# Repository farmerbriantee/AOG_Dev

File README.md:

# AOG Development

Like AgOpenGPS but not.<br>
This version is constantly under development.<br>
Some differences:<br>
The fields and vehicles are **not** backwards compatible. They are stored in ```C:\Documents\AOG```, not ```C:\Documents\AgOpenGPS``` like previous versions were. 

Instead of one vehicle file where everything was stored, there is now a "User" file where the display settings are stored, regardless of which vehicle is used. The Vehicle and Tool are also separated, so you can have one vehicle per tractor, and a Tool for each implement. Fields are also changed, so you can have multiple Jobs per field, saving you from needing to create "Fields From Existing". The painted area is saved in the Job file, and can be re-opened whenever you want. 

AOG also supports the TM 171 IMU via USB. 

AOG also has builtin Rate Control.

AOG also has builtin Active Tool Steering.

AgIO natively supports GPS Out via serial bus, so the GPS_Out application is not required.

There are other minor differences, but these are the main ones.

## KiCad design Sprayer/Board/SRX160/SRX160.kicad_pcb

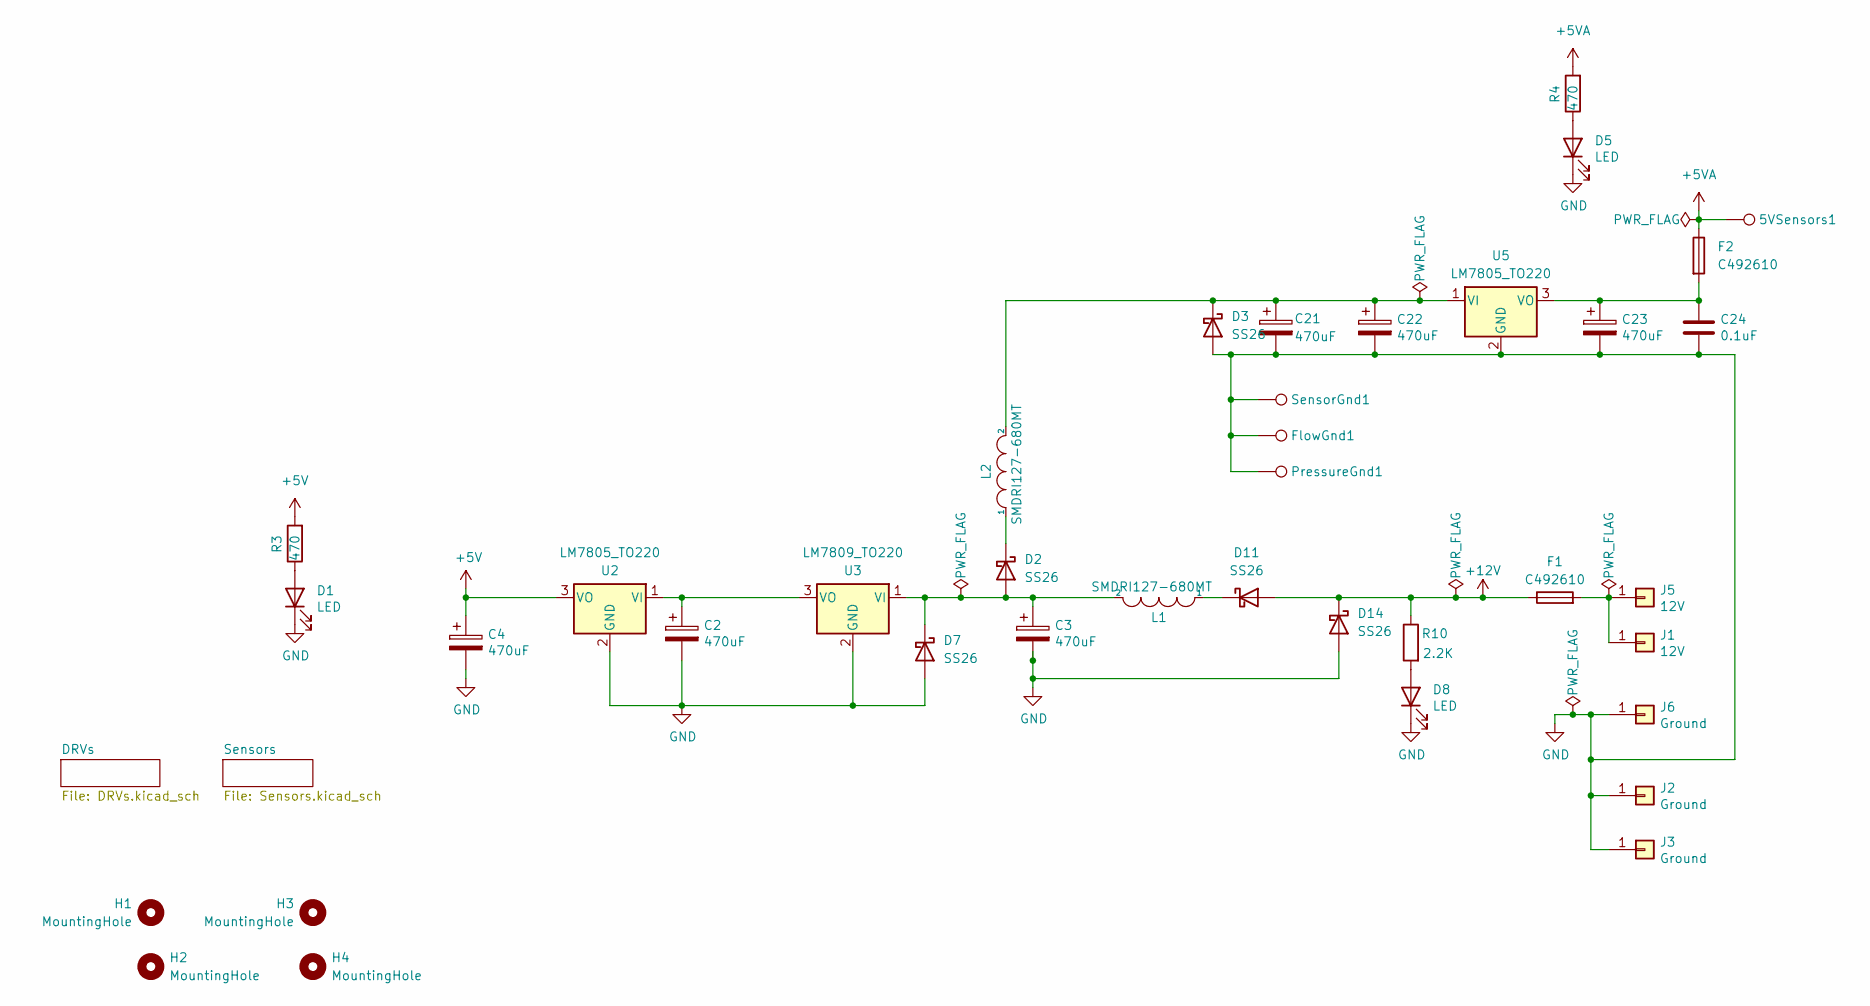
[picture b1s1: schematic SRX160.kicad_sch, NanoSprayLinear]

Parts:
5VSensors1: WirePad; SolderWirePad16
C2, C3, C4, C21, C22, C23: 470uF; CP_Elec_10x10.5
C24: 0.1uF; C_0603_1608Metric
D1, D5, D8: LED; LED_0603_1608Metric
D2, D3, D7, D11, D14: SS26; D_SMA
F1, F2: C492610; Fuse_Holder_C492610
FlowGnd1: WirePad; SolderWirePad16
H1, H2, H3, H4: MountingHole; MountingHole_5.3mm_M5_DIN965_Pad
J1, J5: 12V; PowerPin
J2, J3, J6: Ground; PowerPin
L1, L2: SMDRI127-680MT; TMPA1265SP-101MN-D
PressureGnd1: WirePad; SolderWirePad16
R3, R4: 470; R_0603_1608Metric
R10: 2.2K; R_0603_1608Metric
SensorGnd1: WirePad; SolderWirePad16
U2, U5: LM7805_TO220; TO-220-3_Vertical
U3: LM7809_TO220; TO-220-3_Vertical

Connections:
+5V: C4.1, R3.2, U2.3 (VO); also elsewhere on the board
+5VA: 5VSensors1.1, F2.1, R4.2; also elsewhere on the board
+12V: D11.2 (A), D14.1 (K), F1.1, R10.1; also elsewhere on the board
GND: C2.2, C3.2, C4.2, C21.2, C22.2, C23.2, C24.2, D1.1 (K), D3.2 (A), D5.1 (K), D7.2 (A), D8.1 (K), D14.2 (A), FlowGnd1.1, J2.1, J3.1, J6.1, PressureGnd1.1, SensorGnd1.1, U2.2 (GND), U3.2 (GND), U5.2 (GND); also elsewhere on the board
unnamed: D1.2 (A), R3.1
unnamed: C3.1, D2.2 (A), D7.1 (K), L1.2, U3.1 (VI)
unnamed: D2.1 (K), L2.1
unnamed: C21.1, C22.1, D3.1 (K), L2.2, U5.1 (VI)
unnamed: D5.2 (A), R4.1
unnamed: D8.2 (A), R10.2
unnamed: D11.1 (K), L1.1
unnamed: F1.2, J1.1, J5.1
unnamed: C2.1, U2.1 (VI), U3.3 (VO)
unnamed: C23.1, C24.1, F2.2, U5.3 (VO)

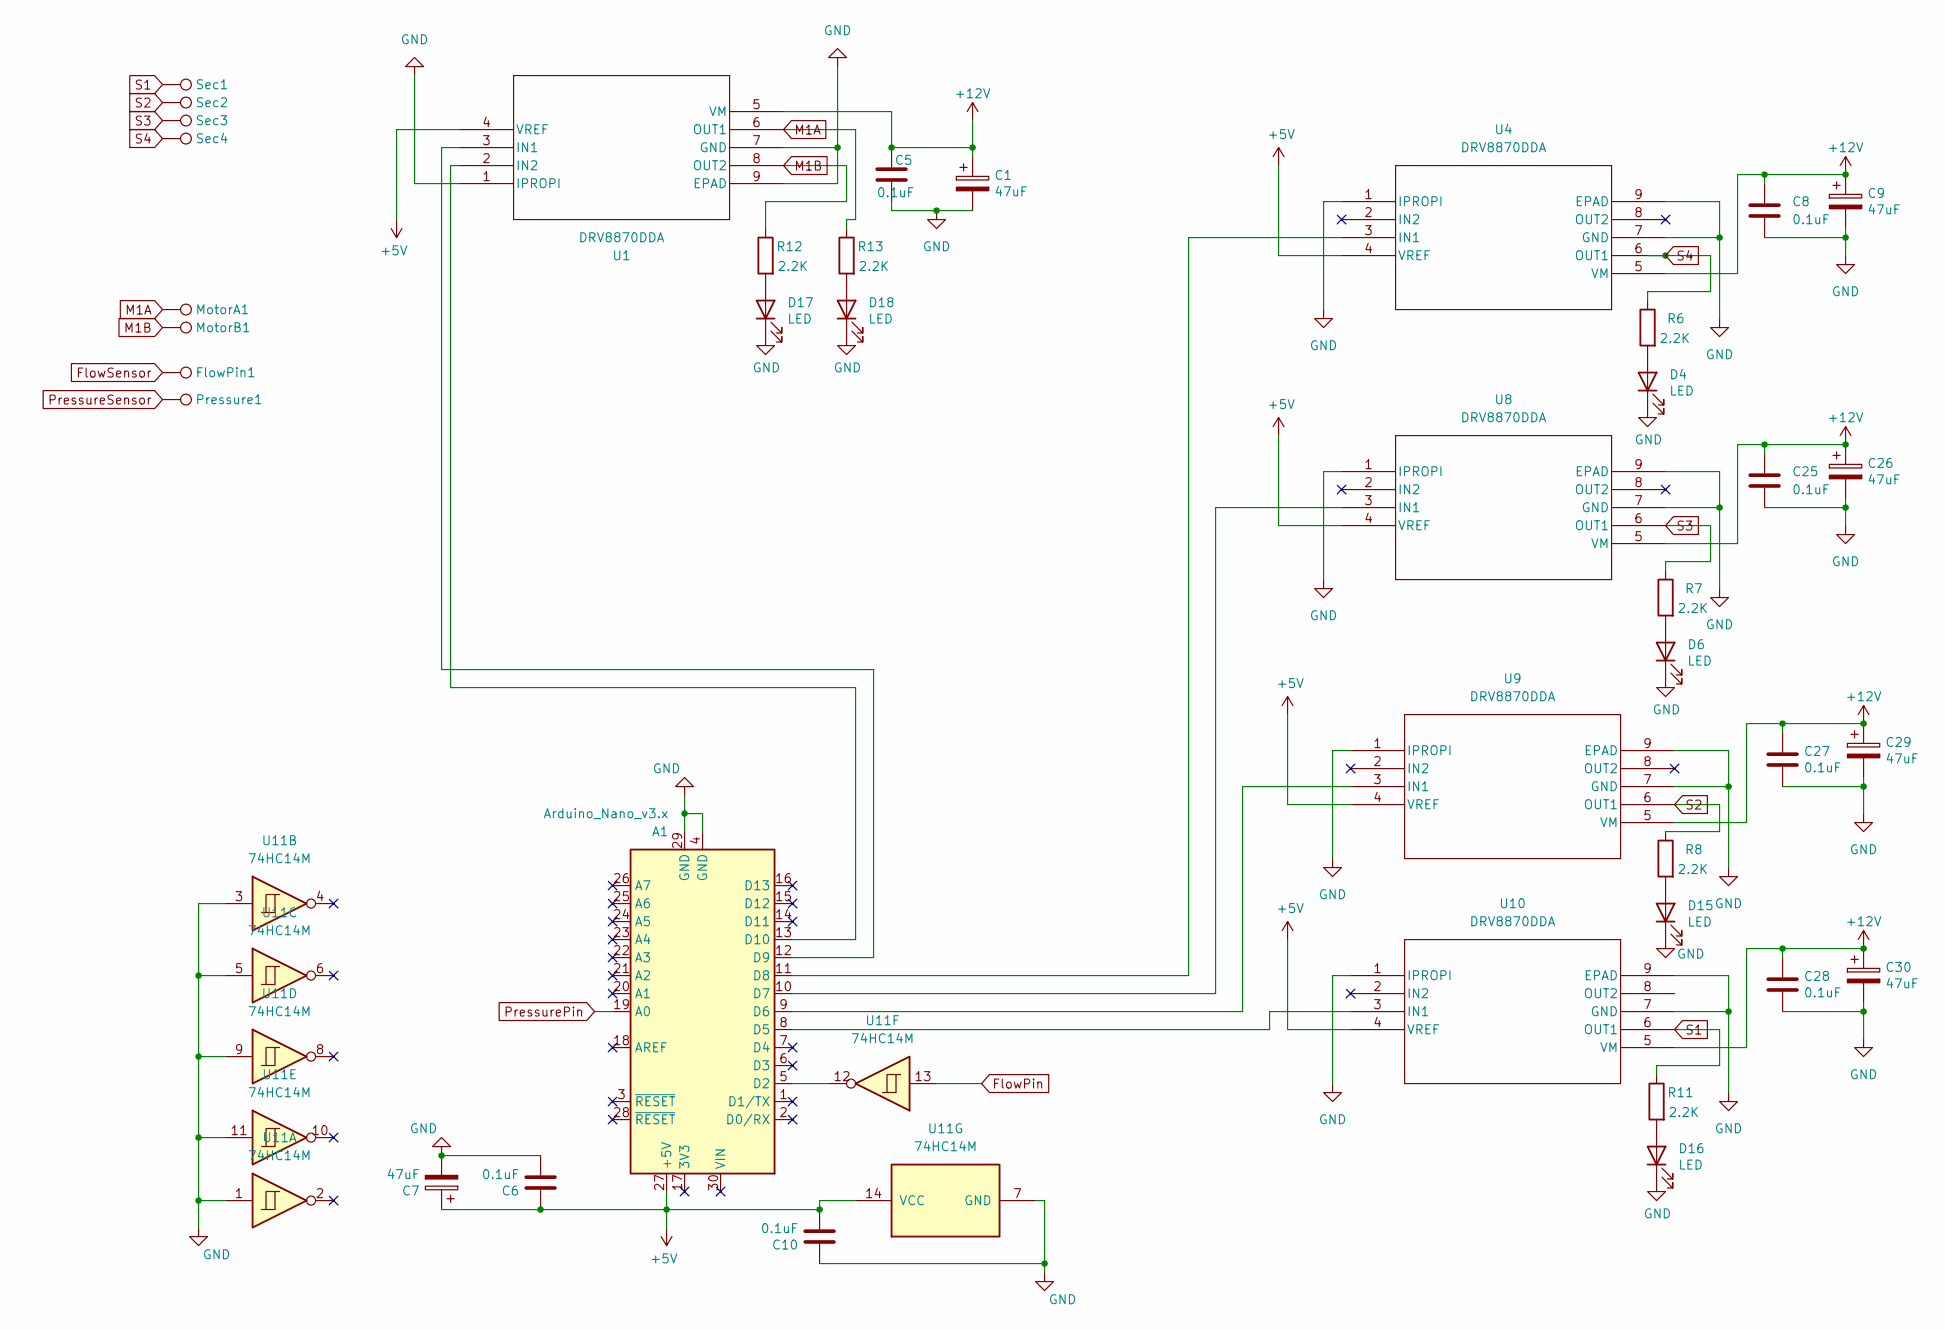
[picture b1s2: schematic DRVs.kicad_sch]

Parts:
A1: Arduino_Nano_v3.x; Arduino_Nano
C1, C7, C9, C26, C29, C30: 47uF; CP_Elec_6.3x5.4
C5, C6, C8, C10, C25, C27, C28: 0.1uF; C_0603_1608Metric
D4, D6, D15, D16, D17, D18: LED; LED_0603_1608Metric
FlowPin1: Flow In; SolderWirePad16
MotorA1: Motor A; SolderWirePad16
MotorB1: Motor B; SolderWirePad16
Pressure1: Pressure; SolderWirePad16
R6, R7, R8, R11, R12, R13: 2.2K; R_0603_1608Metric
Sec1, Sec2: SolderWirePad16
Sec3: Sec 3; SolderWirePad16
Sec4: Sec 4; SolderWirePad16
U1, U4, U8, U9, U10: DRV8870DDA; DRV8251ADDR
U11: 74HC14M; SOIC-14_3.9x8.7mm_P1.27mm

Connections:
+5V: A1.27 (+5V), C6.1, C7.1, C10.2, U1.4 (VREF), U4.4 (VREF), U8.4 (VREF), U9.4 (VREF), U10.4 (VREF), U11.14 (VCC); also elsewhere on the board
+12V: C1.1, C5.1, C8.1, C9.1, C25.1, C26.1, C27.1, C28.1, C29.1, C30.1, U1.5 (VM), U4.5 (VM), U8.5 (VM), U9.5 (VM), U10.5 (VM); also elsewhere on the board
FlowPin: U11.13; also elsewhere on the board
FlowSensor: FlowPin1.1; also elsewhere on the board
GND: A1.4 (GND), A1.29 (GND), C1.2, C5.2, C6.2, C7.2, C8.2, C9.2, C10.1, C25.2, C26.2, C27.2, C28.2, C29.2, C30.2, D4.1 (K), D6.1 (K), D15.1 (K), D16.1 (K), D17.1 (K), D18.1 (K), U1.1 (IPROPI), U1.7 (GND), U1.9 (EPAD), U4.1 (IPROPI), U4.7 (GND), U4.9 (EPAD), U8.1 (IPROPI), U8.7 (GND), U8.9 (EPAD), U9.1 (IPROPI), U9.7 (GND), U9.9 (EPAD), U10.1 (IPROPI), U10.7 (GND), U10.9 (EPAD), U11.1, U11.3, U11.5, U11.7 (GND), U11.9, U11.11; also elsewhere on the board
M1A: MotorA1.1, R13.1, U1.6 (OUT1)
M1B: MotorB1.1, R12.1, U1.8 (OUT2)
unnamed: A1.5 (D2), U11.12
unnamed: A1.8 (D5), U10.3 (IN1)
unnamed: A1.9 (D6), U9.3 (IN1)
unnamed: A1.10 (D7), U8.3 (IN1)
unnamed: A1.11 (D8), U4.3 (IN1)
unnamed: A1.12 (D9), U1.3 (IN1)
unnamed: A1.13 (D10), U1.2 (IN2)
unnamed: D4.2 (A), R6.2
unnamed: D6.2 (A), R7.2
unnamed: D15.2 (A), R8.2
unnamed: D16.2 (A), R11.2
unnamed: D17.2 (A), R12.2
unnamed: D18.2 (A), R13.2
PressurePin: A1.19 (A0); also elsewhere on the board
PressureSensor: Pressure1.1; also elsewhere on the board
S1: R11.1, Sec1.1, U10.6 (OUT1)
S2: R8.1, Sec2.1, U9.6 (OUT1)
S3: R7.1, Sec3.1, U8.6 (OUT1)
S4: R6.1, Sec4.1, U4.6 (OUT1)

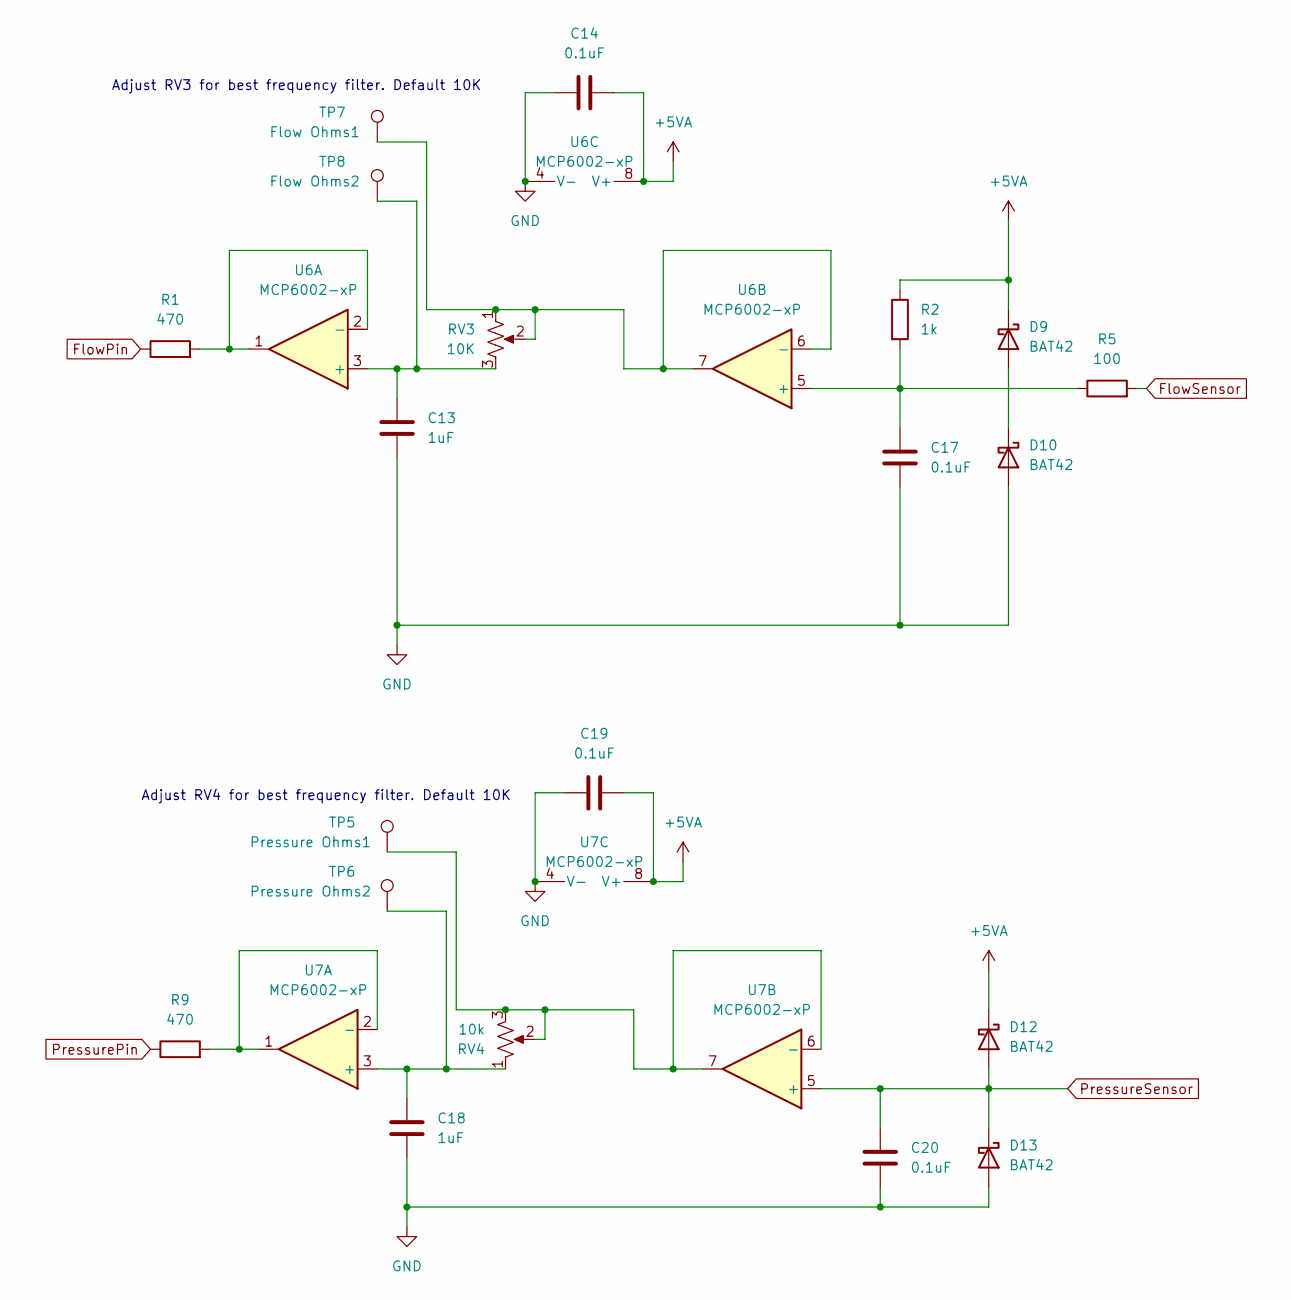
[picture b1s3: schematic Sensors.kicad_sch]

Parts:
C13, C18: 1uF; C_0805_2012Metric
C14, C17, C19, C20: 0.1uF; C_0603_1608Metric
D9, D10, D12, D13: BAT42; SOD-323
R1, R9: 470; C_0603_1608Metric
R2: 1k; R_Axial_DIN0207_L6.3mm_D2.5mm_P10.16mm_Horizontal
R5: 100; R_Axial_DIN0207_L6.3mm_D2.5mm_P10.16mm_Horizontal
RV3: 10K; Potentiometer
RV4: 10k; Potentiometer
TP5: Pressure Ohms1; TestPoint_THTPad_D2.5mm_Drill1.2mm
TP6: Pressure Ohms2; TestPoint_THTPad_D2.5mm_Drill1.2mm
TP7: Flow Ohms1; TestPoint_THTPad_D2.5mm_Drill1.2mm
TP8: Flow Ohms2; TestPoint_THTPad_D2.5mm_Drill1.2mm
U6, U7: MCP6002-xP; SOIC-8_3.9x4.9mm_P1.27mm

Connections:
+5VA: C14.2, C19.2, D9.1 (K), D12.1 (K), R2.1, U6.8 (V+), U7.8 (V+); also elsewhere on the board
FlowPin: R1.1; also elsewhere on the board
FlowSensor: R5.2; also elsewhere on the board
GND: C13.2, C14.1, C17.2, C18.2, C19.1, C20.2, D10.2 (A), D13.2 (A), U6.4 (V-), U7.4 (V-); also elsewhere on the board
unnamed: D9.2 (A), D10.1 (K)
unnamed: C13.1, RV3.3, TP8.1, U6.3 (+)
unnamed: R1.2, U6.1, U6.2 (-)
unnamed: C17.1, R2.2, R5.1, U6.5 (+)
unnamed: RV3.1, RV3.2, TP7.1, U6.6 (-), U6.7
unnamed: C18.1, RV4.1, TP6.1, U7.3 (+)
unnamed: R9.2, U7.1, U7.2 (-)
unnamed: RV4.2, RV4.3, TP5.1, U7.6 (-), U7.7
PressurePin: R9.1; also elsewhere on the board
PressureSensor: C20.1, D12.2 (A), D13.1 (K), U7.5 (+); also elsewhere on the board

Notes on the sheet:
Adjust RV3 for best frequency filter. Default 10K
Adjust RV4 for best frequency filter. Default 10K

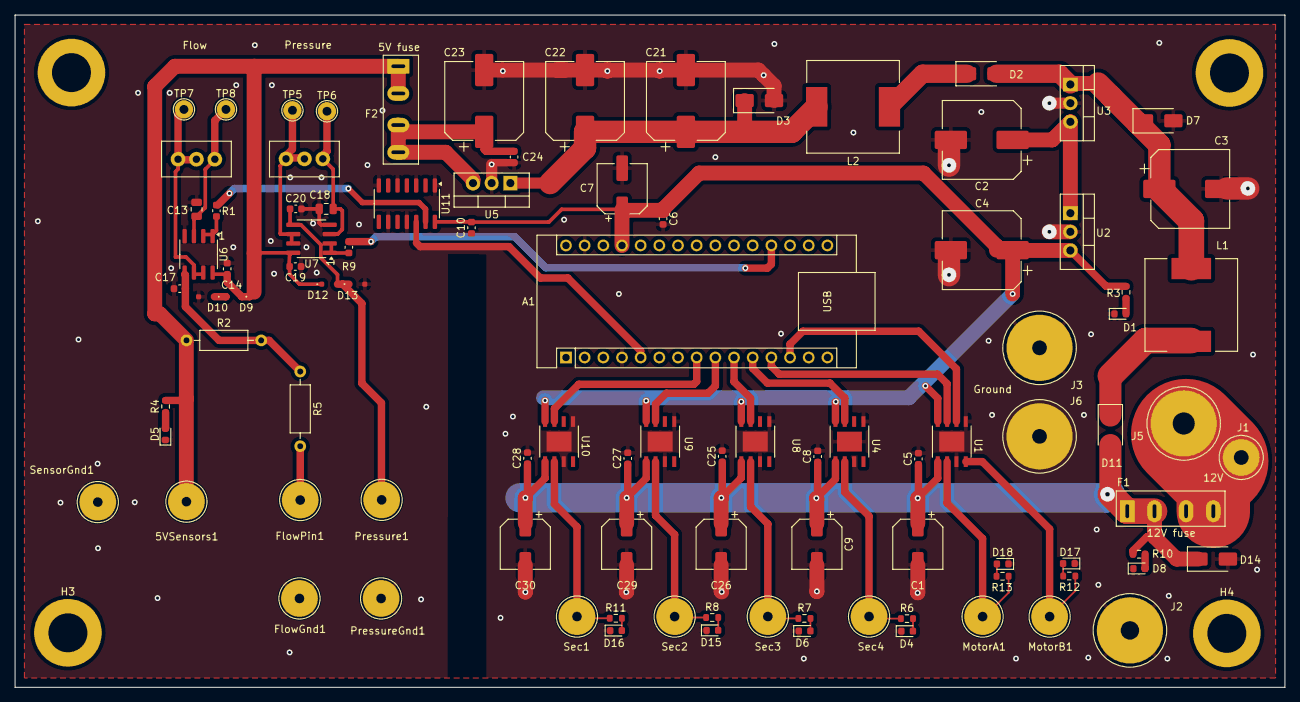
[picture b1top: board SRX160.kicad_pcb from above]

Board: 2 copper layers, 172.7 x 91.4 mm, 100 parts (0 on the bottom side), 45 nets.

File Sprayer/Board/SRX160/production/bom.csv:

Designator,Footprint,Quantity,Value,LCSC Part #
"C1, C26, C29, C30, C7, C9",CP_Elec_6.3x5.4,6,47uF,
"C13, C18",0805,2,1uF,C28323
"C14, C17, C19, C20",0603,4,0.1uF,C187860
"C2, C21, C22, C23, C3, C4",CP_Elec_10x10.5,6,470uF,
"C24, C25, C27, C28, C5, C6, C8",0603,7,0.1uF,
"D1, D15, D16, D17, D18, D4, D5, D6, D8",0603,9,LED,
"D10, D12, D13, D9",SOD-323,4,BAT42,
"D11, D14, D2, D3, D7",D_SMA,5,SS26,C5350986
"F1, F2",Fuse_Holder_C492610,2,C492610,C492610
"L1, L2",TMPA1265SP-101MN-D,2,SMDRI127-680MT,
"R1, R9",0603,2,470,C23179
R10,0603,1,2.2K,C4190
"R11, R12, R13, R6, R7, R8",0603,6,2.2K,
"R3, R4",0603,2,470,
"RV3, RV4",Potentiometer,2,10K,C34846
"U1, U10, U4, U8, U9",DRV8251ADDR,5,DRV8870DDA,C86590
"U2, U5",TO-220-3_Vertical,2,LM7805_TO220,C5444281
U3,TO-220-3_Vertical,1,LM7809_TO220,C507141
U6,SOIC127P600X175-8N,1,MCP6002-xP,
U7,SOIC127P600X175-8N,1,MCP6002-xP,C7377

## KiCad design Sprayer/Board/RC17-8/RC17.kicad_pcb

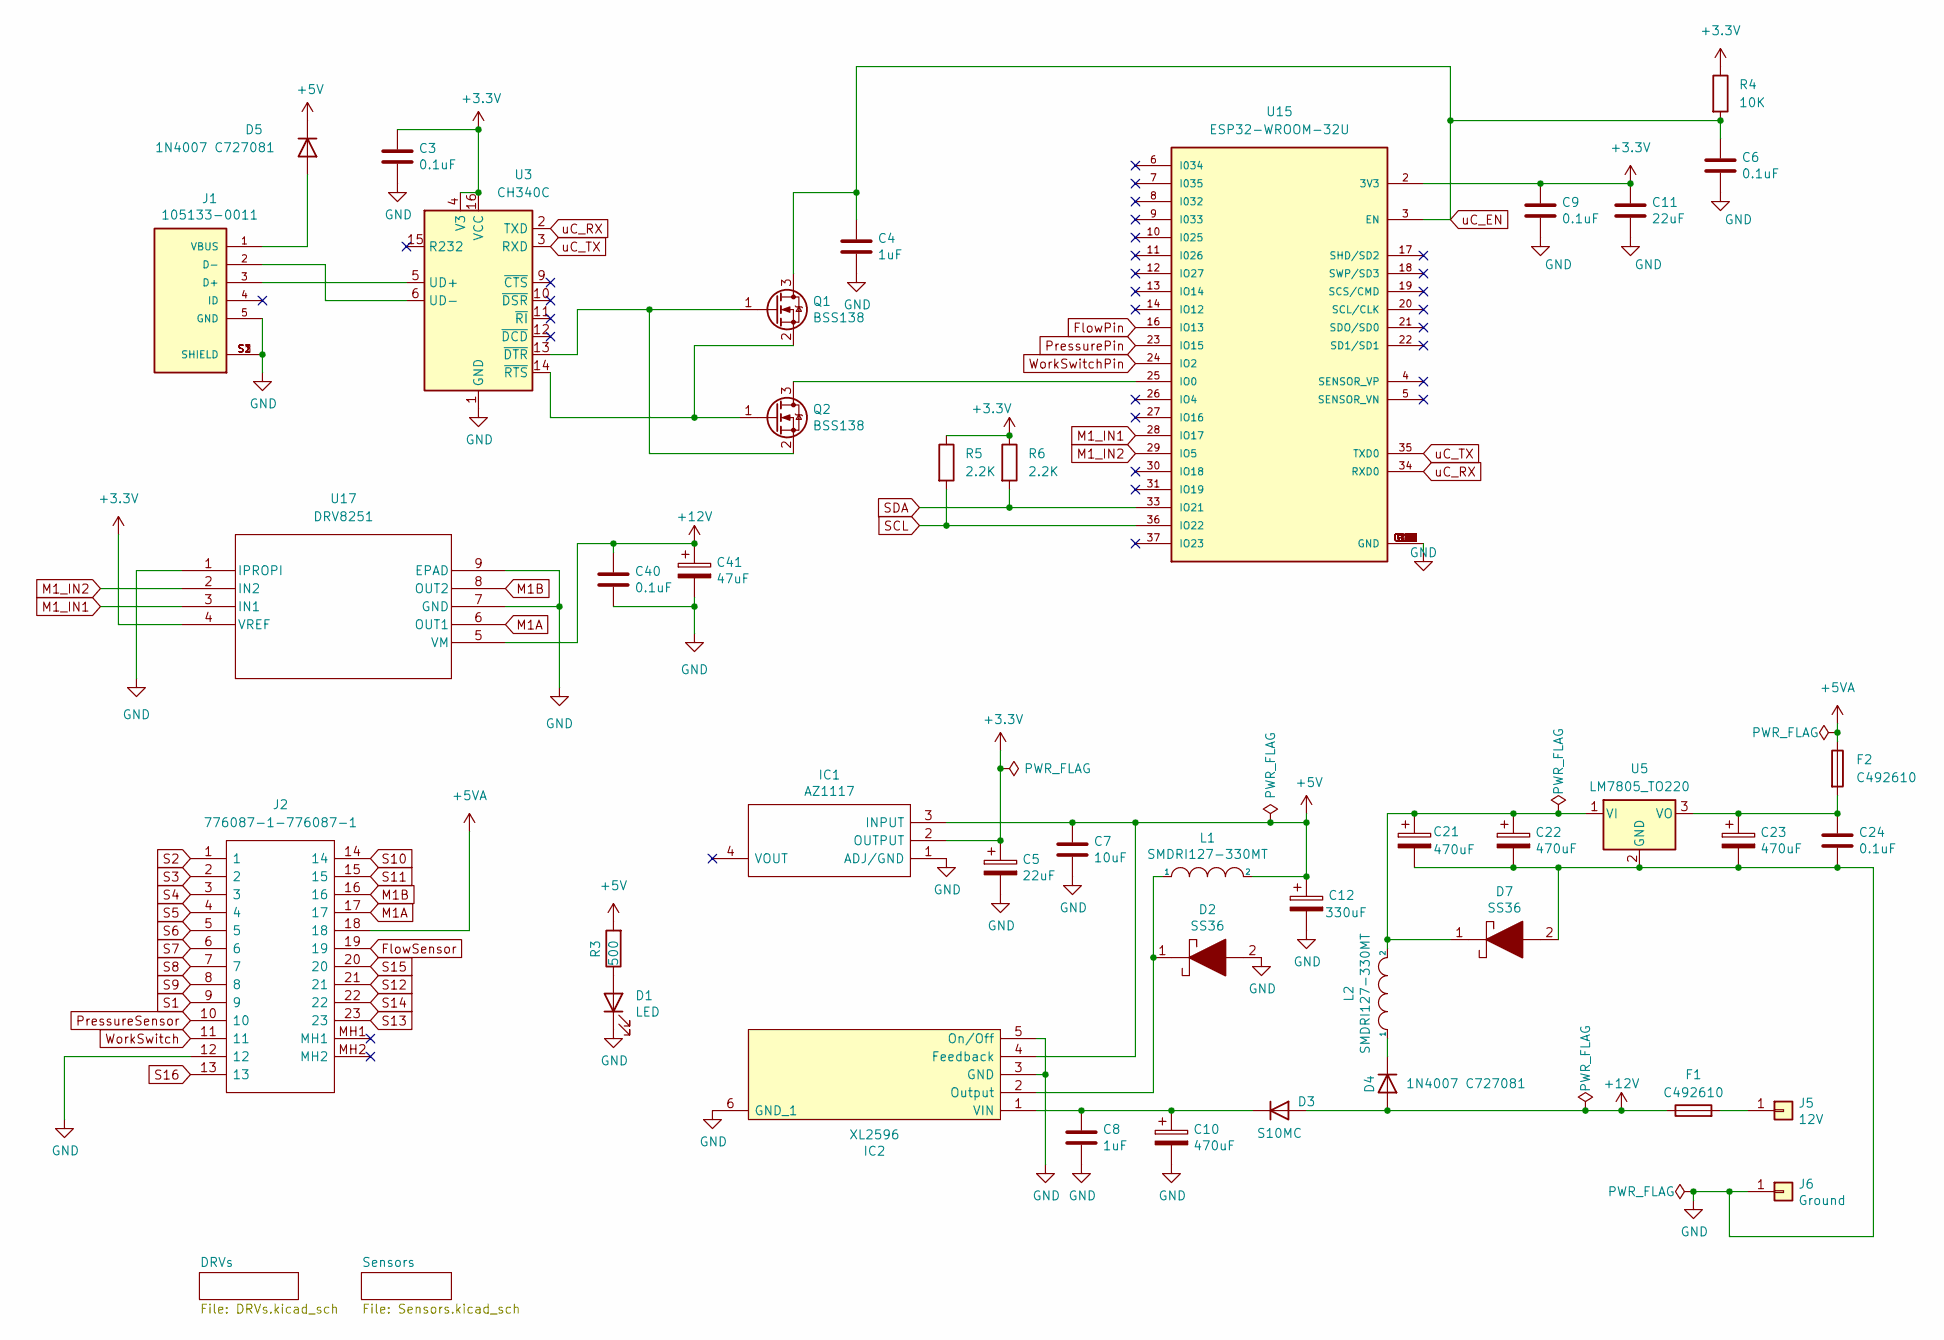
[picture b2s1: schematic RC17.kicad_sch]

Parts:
C3, C6, C9, C24, C40: 0.1uF; C_0603_1608Metric
C4, C8: 1uF; C_0805_2012Metric
C5, C11: 22uF; C_0603_1608Metric
C7: 10uF; C_0805_2012Metric
C10, C21, C22, C23: 470uF; CP_Elec_10x10.5
C12: 330uF; CP_Elec_10x10.5
C41: 47uF; CP_Elec_6.3x5.4
D1: LED; LED_0603_1608Metric
D2, D7: SS36; SMA(DO-214AC)
D3: S10MC; D_SMC_larger_pads
D4, D5: 1N4007 C727081; SMA(DO-214AC)
F1, F2: C492610; Fuse_Holder_C492610
IC1: AZ1117; SOT-223; Mouser Part Number 621-AZ1117CH-3.3TRG1
IC2: XL2596; TO263-5L
J1: 105133-0011; MOLEX_105133-0011; PARTREV C
J2: 776087-1-776087-1; 7760871; Mouser Part Number 571-776087-1
J5: 12V; PowerPin
J6: Ground; PowerPin
L1, L2: SMDRI127-330MT; TMPA1265SP-101MN-D
Q1, Q2: BSS138; SOT-23
R3: 500; R_0603_1608Metric
R4: 10K; R_0603_1608Metric
R5, R6: 2.2K; R_0603_1608Metric
U3: CH340C; SOIC-16_3.9x9.9mm_P1.27mm
U5: LM7805_TO220; TO-220-3_Vertical
U15: ESP32-WROOM-32U; XCVR_ESP32-WROOM-32U; PARTREV V1.9
U17: DRV8251; DRV8251ADDR

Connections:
+3.3V: C3.1, C5.1, C9.1, C11.1, IC1.2 (OUTPUT), R4.1, R5.1, R6.1, U3.4 (V3), U3.16 (VCC), U15.2 (3V3), U17.4 (VREF); also elsewhere on the board
+5V: C7.1, C12.1, D5.1 (K), IC1.3 (INPUT), IC2.4 (Feedback), L1.2, R3.2
+5VA: F2.1, J2.18; also elsewhere on the board
+12V: C40.1, C41.1, D3.2 (A), D4.2 (A), F1.1, U17.5 (VM); also elsewhere on the board
FlowPin: U15.16 (IO13); also elsewhere on the board
FlowSensor: J2.19; also elsewhere on the board
GND: C3.2, C4.2, C5.2, C6.2, C7.2, C8.2, C9.2, C10.2, C11.2, C12.2, C21.2, C22.2, C23.2, C24.2, C40.2, C41.2, D1.1 (K), D2.2, D7.2, IC1.1 (ADJ/GND), IC2.3 (GND), IC2.5 (On/Off), IC2.6 (GND_1), J1.5 (GND), J1.S1 (SHIELD), J1.S2 (SHIELD), J1.S3 (SHIELD), J2.12, J6.1, U3.1 (GND), U5.2 (GND), U15.1 (GND), U15.15 (GND), U15.38 (GND), U15.G.1 (GND), U15.G.2 (GND), U15.G.4 (GND), U15.G.5 (GND), U15.G.6 (GND), U15.G.7 (GND), U15.G.8 (GND), U15.G.9 (GND), U15.G.10 (GND), U15.G.11 (GND), U15.G.12 (GND), U15.G.13 (GND), U15.G.14 (GND), U15.G.15 (GND), U15.G.16 (GND), U15.G.17 (GND), U15.G.18 (GND), U15.G.19 (GND), U15.G.20 (GND), U15.G.21 (GND), U15.G.22 (GND), U17.1 (IPROPI), U17.7 (GND), U17.9 (EPAD); also elsewhere on the board
M1A: J2.17, U17.6 (OUT1)
M1B: J2.16, U17.8 (OUT2)
M1_IN1: U15.28 (IO17), U17.3 (IN1)
M1_IN2: U15.29 (IO5), U17.2 (IN2)
unnamed: D1.2 (A), R3.1
unnamed: C8.1, C10.1, D3.1 (K), IC2.1 (VIN)
unnamed: D4.1 (K), L2.1
unnamed: D5.2 (A), J1.1 (VBUS)
unnamed: D2.1, IC2.2 (Output), L1.1
unnamed: J1.3 (D+), U3.5 (UD+)
unnamed: J1.2 (D-), U3.6 (UD-)
unnamed: F1.2, J5.1
unnamed: Q1.1 (G), Q2.2 (S), U3.13 (~DTR)
unnamed: Q1.2 (S), Q2.1 (G), U3.14 (~RTS)
unnamed: Q2.3 (D), U15.25 (IO0)
unnamed: C21.1, C22.1, D7.1, L2.2, U5.1 (VI)
unnamed: C23.1, C24.1, F2.2, U5.3 (VO)
PressurePin: U15.23 (IO15); also elsewhere on the board
PressureSensor: J2.10; also elsewhere on the board
S1: J2.9; also elsewhere on the board
S2: J2.1; also elsewhere on the board
S3: J2.2; also elsewhere on the board
S4: J2.3; also elsewhere on the board
S5: J2.4; also elsewhere on the board
S6: J2.5; also elsewhere on the board
S7: J2.6; also elsewhere on the board
S8: J2.7; also elsewhere on the board
S9: J2.8; also elsewhere on the board
S10: J2.14; also elsewhere on the board
S11: J2.15; also elsewhere on the board
S12: J2.21; also elsewhere on the board
S13: J2.23; also elsewhere on the board
S14: J2.22; also elsewhere on the board
S15: J2.20; also elsewhere on the board
S16: J2.13; also elsewhere on the board
SCL: R5.2, U15.36 (IO22); also elsewhere on the board
SDA: R6.2, U15.33 (IO21); also elsewhere on the board
WorkSwitch: J2.11; also elsewhere on the board
WorkSwitchPin: U15.24 (IO2); also elsewhere on the board
uC_EN: C4.1, C6.1, Q1.3 (D), R4.2, U15.3 (EN)
uC_RX: U3.2 (TXD), U15.34 (RXD0)
uC_TX: U3.3 (RXD), U15.35 (TXD0)

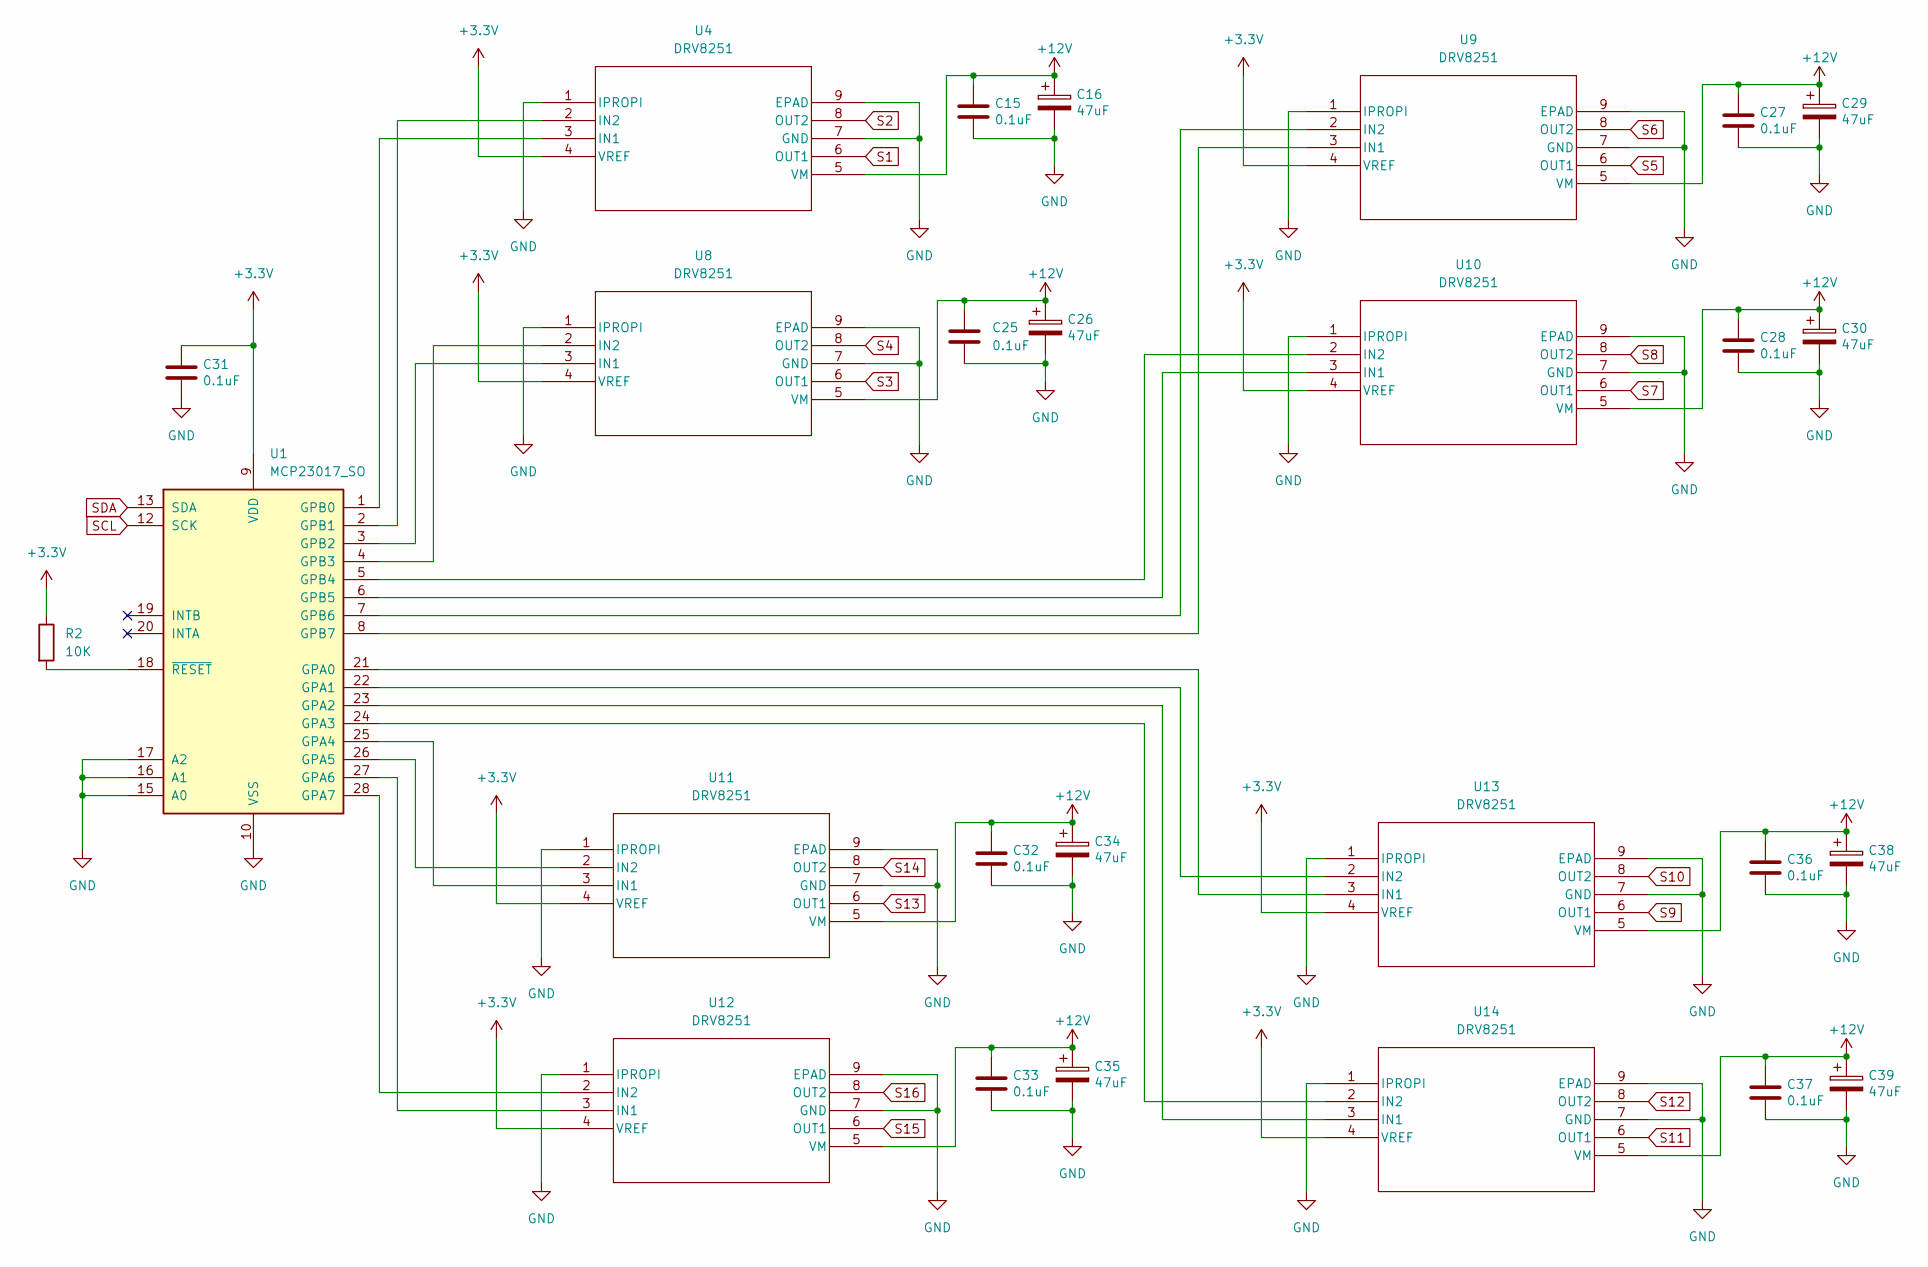
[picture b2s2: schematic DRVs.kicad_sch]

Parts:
C15, C25, C27, C28, C31, C32, C33, C36, C37: 0.1uF; C_0603_1608Metric
C16, C26, C29, C30, C34, C35, C38, C39: 47uF; CP_Elec_6.3x5.4
R2: 10K; R_0603_1608Metric
U1: MCP23017_SO; SOIC-28W_7.5x17.9mm_P1.27mm
U4, U8, U9, U10, U11, U12, U13, U14: DRV8251; DRV8251ADDR

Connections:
+3.3V: C31.1, R2.1, U1.9 (VDD), U4.4 (VREF), U8.4 (VREF), U9.4 (VREF), U10.4 (VREF), U11.4 (VREF), U12.4 (VREF), U13.4 (VREF), U14.4 (VREF); also elsewhere on the board
+12V: C15.1, C16.1, C25.1, C26.1, C27.1, C28.1, C29.1, C30.1, C32.1, C33.1, C34.1, C35.1, C36.1, C37.1, C38.1, C39.1, U4.5 (VM), U8.5 (VM), U9.5 (VM), U10.5 (VM), U11.5 (VM), U12.5 (VM), U13.5 (VM), U14.5 (VM); also elsewhere on the board
GND: C15.2, C16.2, C25.2, C26.2, C27.2, C28.2, C29.2, C30.2, C31.2, C32.2, C33.2, C34.2, C35.2, C36.2, C37.2, C38.2, C39.2, U1.10 (VSS), U1.15 (A0), U1.16 (A1), U1.17 (A2), U4.1 (IPROPI), U4.7 (GND), U4.9 (EPAD), U8.1 (IPROPI), U8.7 (GND), U8.9 (EPAD), U9.1 (IPROPI), U9.7 (GND), U9.9 (EPAD), U10.1 (IPROPI), U10.7 (GND), U10.9 (EPAD), U11.1 (IPROPI), U11.7 (GND), U11.9 (EPAD), U12.1 (IPROPI), U12.7 (GND), U12.9 (EPAD), U13.1 (IPROPI), U13.7 (GND), U13.9 (EPAD), U14.1 (IPROPI), U14.7 (GND), U14.9 (EPAD); also elsewhere on the board
unnamed: U1.21 (GPA0), U13.3 (IN1)
unnamed: U1.22 (GPA1), U13.2 (IN2)
unnamed: U1.23 (GPA2), U14.3 (IN1)
unnamed: U1.24 (GPA3), U14.2 (IN2)
unnamed: U1.25 (GPA4), U11.3 (IN1)
unnamed: U1.26 (GPA5), U11.2 (IN2)
unnamed: U1.27 (GPA6), U12.3 (IN1)
unnamed: U1.28 (GPA7), U12.2 (IN2)
unnamed: U1.1 (GPB0), U4.3 (IN1)
unnamed: U1.2 (GPB1), U4.2 (IN2)
unnamed: U1.3 (GPB2), U8.3 (IN1)
unnamed: U1.4 (GPB3), U8.2 (IN2)
unnamed: U1.5 (GPB4), U10.2 (IN2)
unnamed: U1.6 (GPB5), U10.3 (IN1)
unnamed: U1.7 (GPB6), U9.2 (IN2)
unnamed: U1.8 (GPB7), U9.3 (IN1)
unnamed: R2.2, U1.18 (~RESET)
S1: U4.6 (OUT1); also elsewhere on the board
S2: U4.8 (OUT2); also elsewhere on the board
S3: U8.6 (OUT1); also elsewhere on the board
S4: U8.8 (OUT2); also elsewhere on the board
S5: U9.6 (OUT1); also elsewhere on the board
S6: U9.8 (OUT2); also elsewhere on the board
S7: U10.6 (OUT1); also elsewhere on the board
S8: U10.8 (OUT2); also elsewhere on the board
S9: U13.6 (OUT1); also elsewhere on the board
S10: U13.8 (OUT2); also elsewhere on the board
S11: U14.6 (OUT1); also elsewhere on the board
S12: U14.8 (OUT2); also elsewhere on the board
S13: U11.6 (OUT1); also elsewhere on the board
S14: U11.8 (OUT2); also elsewhere on the board
S15: U12.6 (OUT1); also elsewhere on the board
S16: U12.8 (OUT2); also elsewhere on the board
SCL: U1.12 (SCK); also elsewhere on the board
SDA: U1.13 (SDA); also elsewhere on the board
